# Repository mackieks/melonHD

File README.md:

# melonHD 🍈

 ## Purchase melonHD on [Flashfi.re](https://flashfi.re)
 
 melonHD is a video converter module based around Lontium Semiconductor's LT6711A. It accepts an HDMI 2.0 input signal (up to 2160p) and outputs USB-C DisplayPort 1.2 Alt Mode. 

 The module is designed to allow [portablizers](https://bitbuilt.net/forums/index.php) to add USB-C video output to DIY handheld video game systems, and therefore does not expose the HDMI DDC connections. As such, compatibility with PCs and other HDMI sources which rely on EDID is not guaranteed. 
 
 For legal reasons, the melonHD module itself is not open source. It's available for purchase on [Flashfire](https://flashfi.re), my webstore. This repository contains documentation, usage guidelines, and an open source carrier board reference design.

 ## Features

- [x] Super compact 17 x 13mm 0.8mm-thick castellated PCB
- [x] 480p - 2160p HDMI 2.0 input and USB-C DP 1.2 Alt Mode output
- [x] Pin-strappable VBUS PDO selection: 5V/3A, 9V/3A, 12V/3A, or 15V/3A
- [x] Powered directly from 5V - 15V VBUS with onboard voltage regulators
- [x] HPD (hotplug detect) output pin: high for DP Alt Mode contracts, low for power-only contracts

## Usage

melonHD is powered by the downstream-facing port. This can be a little confusing if you're unfamiliar with the USB-C protocol. Basically, your USB-C monitor needs to be able to provide power to melonHD, while melonHD sends it video data. Most DP Alt Mode sinks support this mode of operation.

The reason melonHD works this way is so it can request power to charge your portable's batteries while your portable is docked. This is identical to how a Nintendo Switch works. Please see the diagram for a more detailed breakdown.

One key feature of melonHD is the customized LT6711A firmware, which allows the user to select what VBUS voltage the module requests from the downstream-facing port. Based on how you pinstrap the module, you can request 5V/3A, 9V/3A, 12V/3A, or 15V/3A. This lets you charge your portable's batteries quickly without sacrificing DP Alt Mode output. Of course, whether you can get higher voltages depends on the capabilities of the downstream port you connect to.

Also, the melonHD module has an "HPD" output pin. This pin is low when melonHD negotiates for a power-only contract, such as when you plug a charger into the USB-C port. But when you plug in a USB-C monitor, melonHD will negotiate a DP Alt Mode contract and the HPD pin will go high. This is useful for enabling GCVideo DVI only when a USB-C monitor is connected, and not when a charger is connected. You could also use it to turn off your portable's screen when an external display is connected, just like a Nintendo Switch.

## License
Carrier board is licensed under Solderpad Hardware License v2.1

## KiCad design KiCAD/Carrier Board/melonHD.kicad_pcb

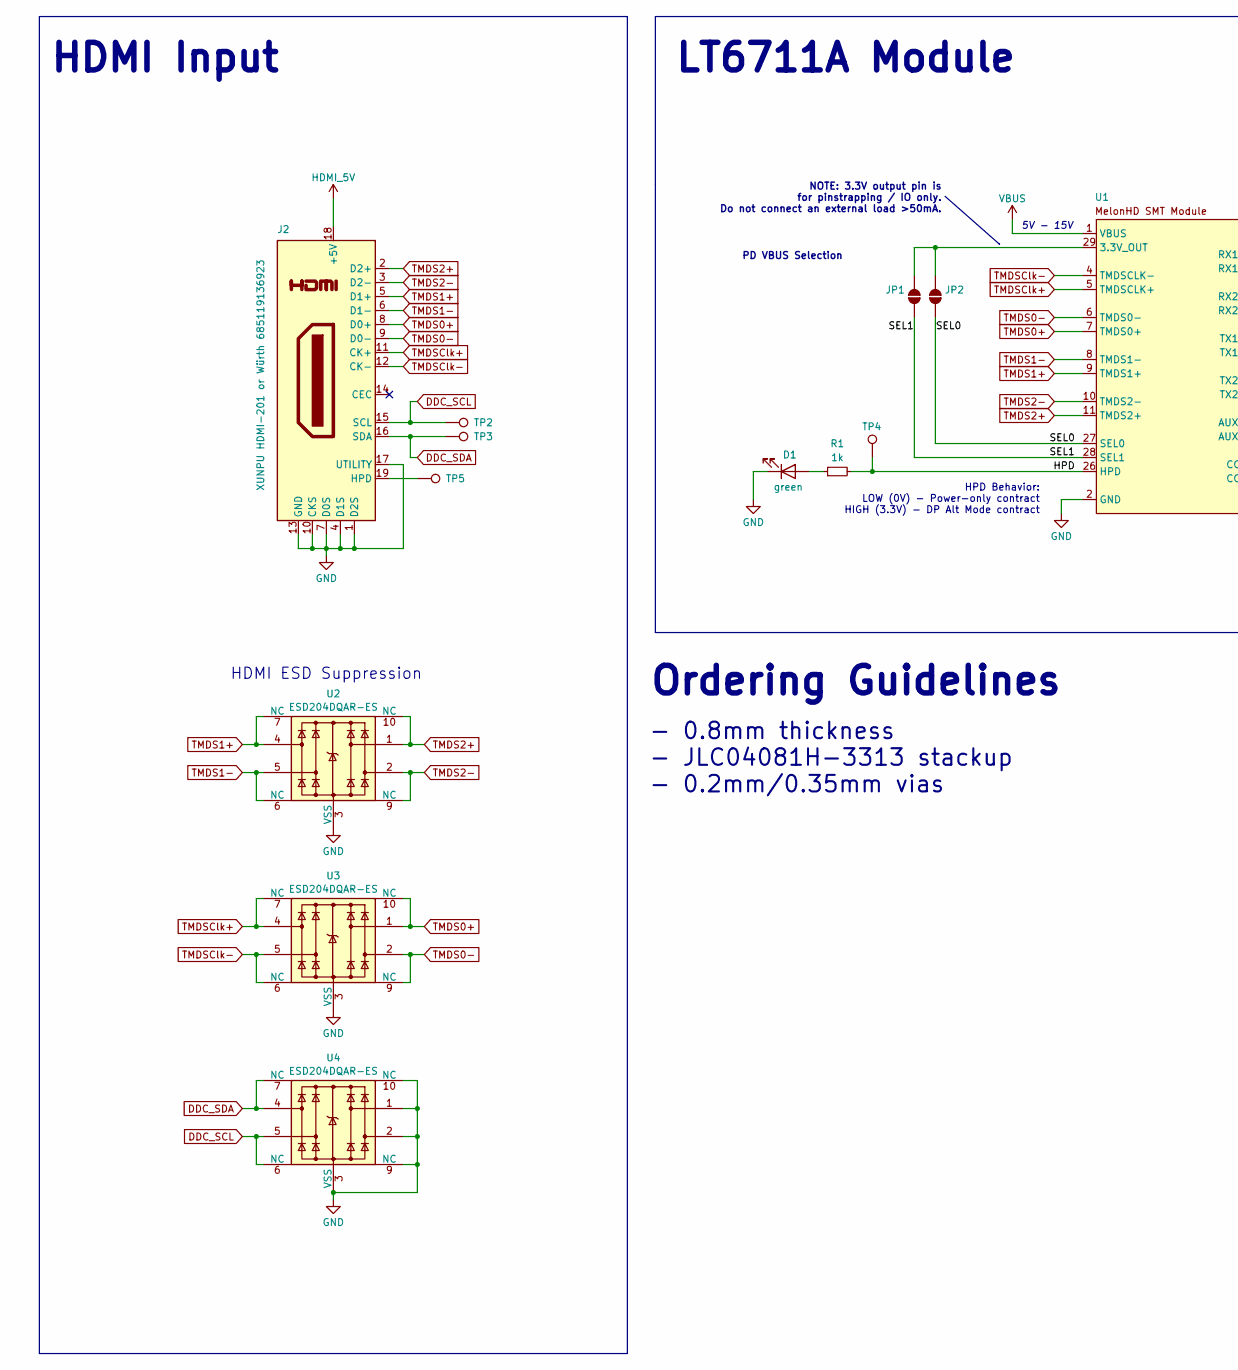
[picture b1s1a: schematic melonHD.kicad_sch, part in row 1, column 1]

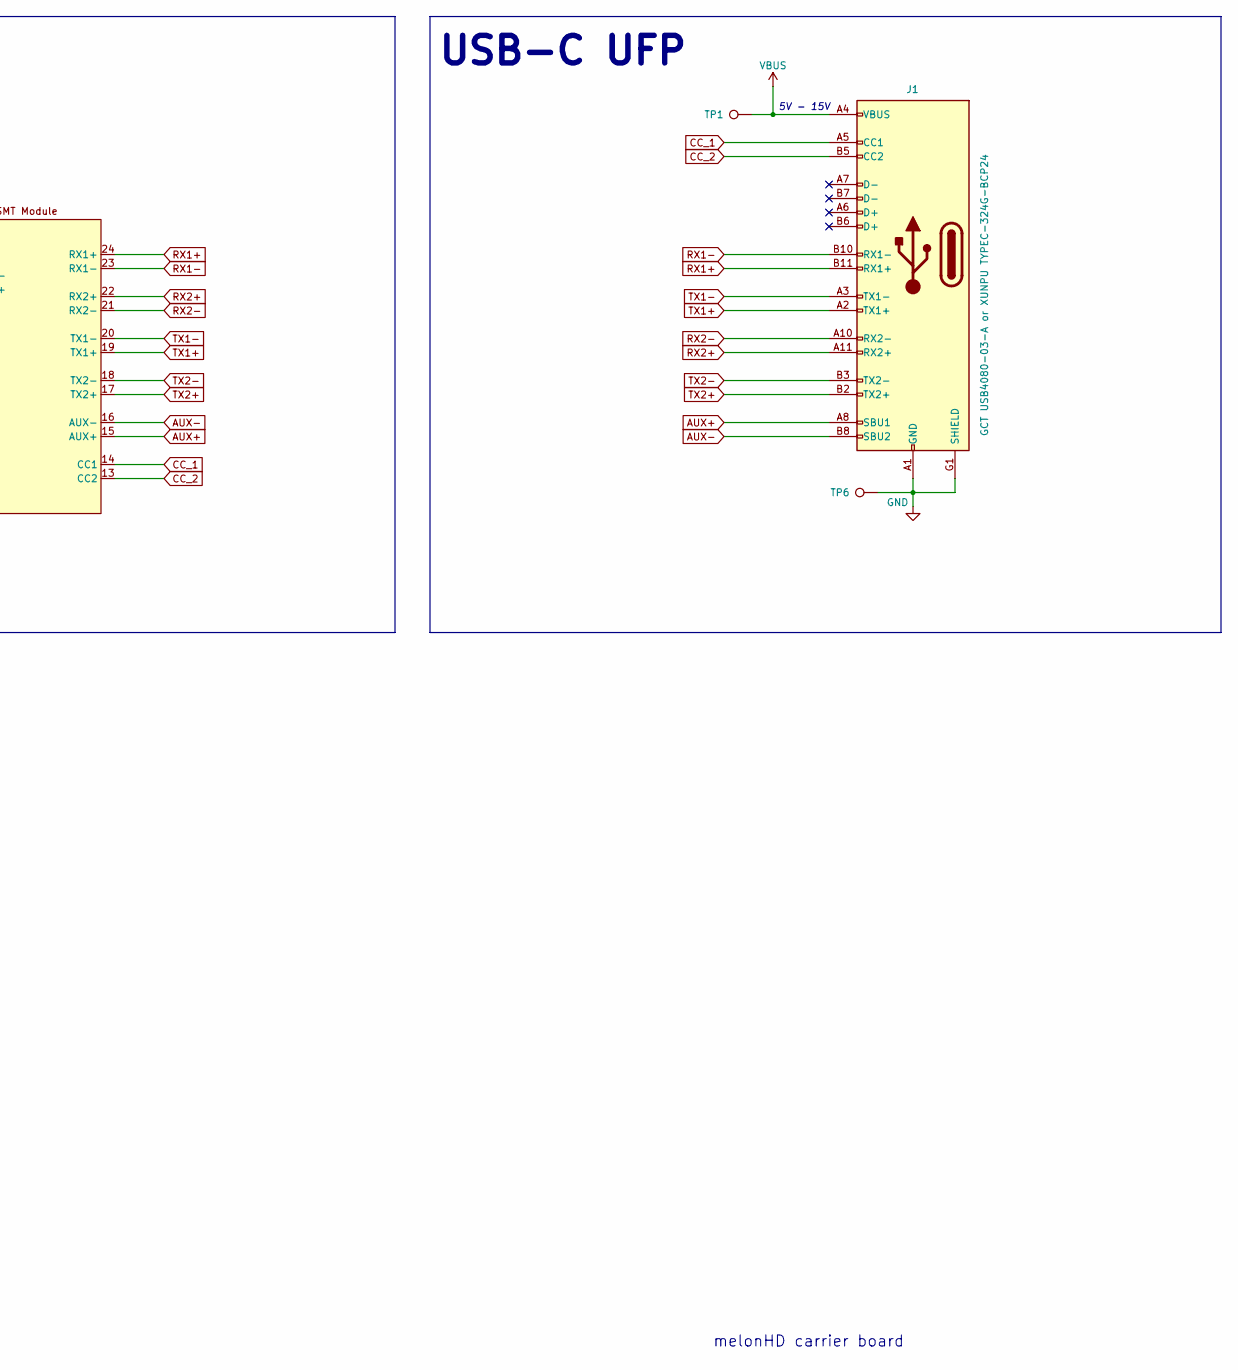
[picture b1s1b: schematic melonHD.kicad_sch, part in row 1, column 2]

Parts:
D1: green; LED_0603_1608Metric
J1: GCT USB4080-03-A or XUNPU TYPEC-324G-BCP24; GCT_USB4080-03-A_REVA1
J2: XUNPU HDMI-201 or Würth 685119136923; 685119136923
JP1, JP2: SolderJumper_2_Open; SolderJumper-2_P1.3mm_Open_RoundedPad1.0x1.5mm
R1: 1k; R_0603_1608Metric
TP1, TP2, TP3, TP4, TP5, TP6: TestPoint; TestPoint_Pad_D0.75
U1: melonHD_SMT
U2, U3, U4: ESD204DQAR-ES; Diodes_UDFN-10_1.0x2.5mm_P0.5mm

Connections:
/HPD: R1.2, TP4.1, U1.26 (HPD)
/SEL0: JP2.1 (A), U1.27 (SEL0)
/SEL1: JP1.1 (A), U1.28 (SEL1)
AUX+: J1.A8 (SBU1), U1.15 (AUX+)
AUX-: J1.B8 (SBU2), U1.16 (AUX-)
CC_1: J1.A5 (CC1), U1.14 (CC1)
CC_2: J1.B5 (CC2), U1.13 (CC2)
DDC_SCL: J2.15 (SCL), TP2.1, U4.5, U4.6 (NC)
DDC_SDA: J2.16 (SDA), TP3.1, U4.4, U4.7 (NC)
GND: D1.1 (K), J1.1 (SHIELD), J1.A1 (GND), J1.A12 (GND), J1.B1 (GND), J1.B12 (GND), J1.G1 (SHIELD), J1.G2 (SHIELD), J1.G3 (SHIELD), J1.G4 (SHIELD), J2.1 (D2S), J2.4 (D1S), J2.7 (D0S), J2.10 (CKS), J2.13 (GND), J2.17 (UTILITY), J2.20 (GND), J2.21 (GND), J2.22 (GND), J2.23 (GND), TP6.1, U1.2 (GND), U1.3 (GND), U1.12 (GND), U1.25 (GND), U1.30 (GND), U1.31 (GND), U2.3 (VSS), U2.8 (VSS), U3.3 (VSS), U3.8 (VSS), U4.1, U4.2, U4.3 (VSS), U4.8 (VSS), U4.9 (NC), U4.10 (NC)
HDMI_5V: J2.18 (+5V)
unnamed: D1.2 (A), R1.1
unnamed: J2.19 (HPD), TP5.1
unnamed: JP1.2 (B), JP2.2 (B), U1.29 (3.3V_OUT)
RX1+: J1.B11 (RX1+), U1.24 (RX1+)
RX1-: J1.B10 (RX1-), U1.23 (RX1-)
RX2+: J1.A11 (RX2+), U1.22 (RX2+)
RX2-: J1.A10 (RX2-), U1.21 (RX2-)
TMDS0+: J2.8 (D0+), U1.7 (TMDS0+), U3.1, U3.10 (NC)
TMDS0-: J2.9 (D0-), U1.6 (TMDS0-), U3.2, U3.9 (NC)
TMDS1+: J2.5 (D1+), U1.9 (TMDS1+), U2.4, U2.7 (NC)
TMDS1-: J2.6 (D1-), U1.8 (TMDS1-), U2.5, U2.6 (NC)
TMDS2+: J2.2 (D2+), U1.11 (TMDS2+), U2.1, U2.10 (NC)
TMDS2-: J2.3 (D2-), U1.10 (TMDS2-), U2.2, U2.9 (NC)
TMDSClk+: J2.11 (CK+), U1.5 (TMDSCLK+), U3.4, U3.7 (NC)
TMDSClk-: J2.12 (CK-), U1.4 (TMDSCLK-), U3.5, U3.6 (NC)
TX1+: J1.A2 (TX1+), U1.19 (TX1+)
TX1-: J1.A3 (TX1-), U1.20 (TX1-)
TX2+: J1.B2 (TX2+), U1.17 (TX2+)
TX2-: J1.B3 (TX2-), U1.18 (TX2-)
VBUS: J1.A4 (VBUS), J1.A9 (VBUS), J1.B4 (VBUS), J1.B9 (VBUS), TP1.1, U1.1 (VBUS)

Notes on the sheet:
Ordering Guidelines
HDMI ESD Suppression
USB-C UFP
5V - 15V
- 0.8mm thickness - JLC04081H-3313 stackup - 0.2mm/0.35mm vias
HDMI Input
melonHD carrier board
LT6711A Module
NOTE: 3.3V output pin is for pinstrapping / IO only. Do not connect an external load >50mA.
PD VBUS Selection
HPD Behavior: LOW (0V) - Power-only contract HIGH (3.3V) - DP Alt Mode contract

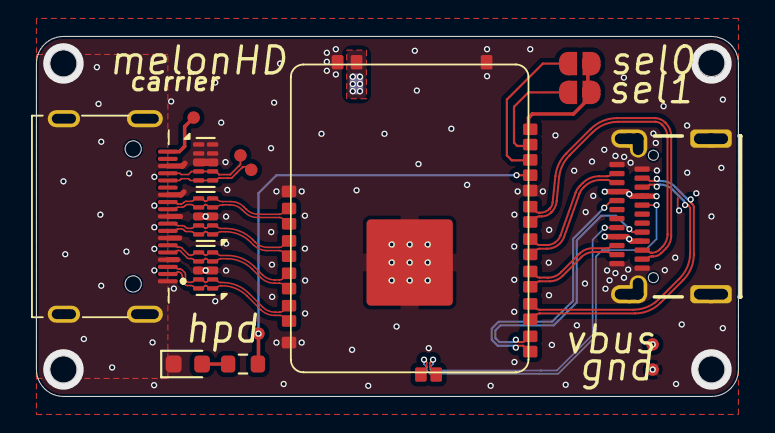
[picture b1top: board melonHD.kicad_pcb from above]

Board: 4 copper layers, 39.0 x 20.0 mm, 16 parts (0 on the bottom side), 30 nets.

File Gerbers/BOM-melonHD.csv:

Comment,Designator,Footprint,LCSC,Quantity
1k,R1,R_0603_1608Metric,C21190,1
green,D1,LED_0603_1608Metric,C2286,1
ESD204DQAR-ES,"U2,U3,U4",Diodes_UDFN-10_1.0x2.5mm_P0.5mm,C2827646,3
XUNPU HDMI-201 or Würth 685119136923,J2,685119136923,C720618,1
XUNPU TYPEC-324G-BCP24 or GCT USB4080-03-A,J1,GCT_USB4080-03-A_REVA1,C920230,1

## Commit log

2025-01-24 add everything
2025-01-24 update pics
2025-02-02 embed fonts + 3d
2025-02-11 Update carrier board
2025-02-11 Update schematic notes
2025-02-11 Add gerbers + CPL + BOM
2025-05-19 Fix dual CC1s to CC2
2025-05-19 Change dual TMDS0- to TMDS0+
2025-05-25 Update module symbol
2025-05-25 Update carrier board and fix 3D embed
